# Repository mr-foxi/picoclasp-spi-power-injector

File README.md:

# picoclasp-spi-power-injector
This is a PCB designed as a picoclasp-molex 6pin SPI pass-through with external power injection from a JST-XHP4. Able to inject either 5VDC directly, or step down 8/36VDC. Contains a 2A fuse for circuitry protection, and a jumper header to select power input.

### Parts List
 - 8/36V-5V_2A = K7805-2000R3 (https://www.mornsun-power.com/html/pdf/K7805-2000R3.html)
 - Pico-Clasp Molex 6pin = 5013310607 (https://www.molex.com/content/dam/molex/molex-dot-com/products/automated/en-us/salesdrawingpdf/501/501331/5013310607_sd.pdf?inline)
 - Pico-Clasp Plug = 5013300600 (https://www.molex.com/content/dam/molex/molex-dot-com/products/automated/en-us/salesdrawingpdf/501/501330/5013300600_sd.pdf?inline)
 - JST-XH4 = S4B-XH-A-1 (https://www.digikey.com/en/products/detail/jst-sales-america-inc/S4B-XH-A-1/9961923)
 - JST Plug = XHP-4 (https://www.jst-mfg.com/product/pdf/eng/eXH.pdf)
 - FUSE_2A = ERB-RE2R00V (https://industrial.panasonic.com/cdbs/www-data/pdf/AFA0000/AFA0000C7.pdf)
 - 3pin Male PCB Jumper Header = XJ8B-0311 (https://www.mouser.com/datasheet/2/307/en_xg8-1539045.pdf)
 - 2pin Jumper = M7582-05 (https://www.mouser.com/datasheet/2/181/M7580-M7583-1134644.pdf)

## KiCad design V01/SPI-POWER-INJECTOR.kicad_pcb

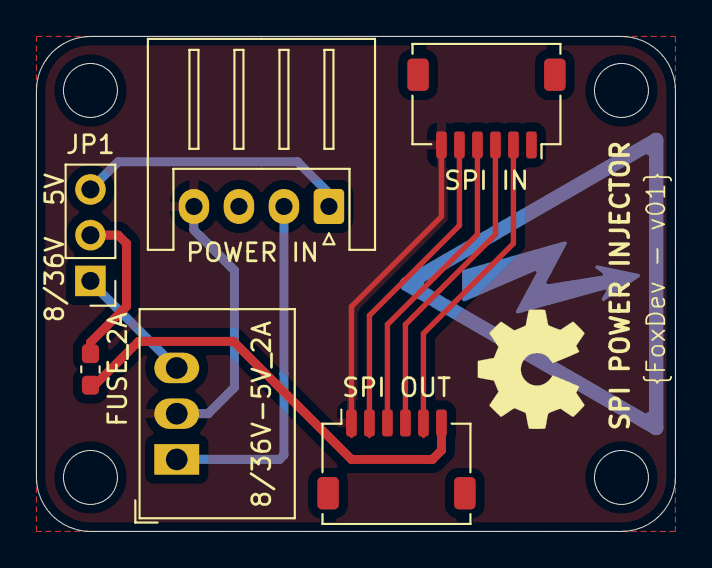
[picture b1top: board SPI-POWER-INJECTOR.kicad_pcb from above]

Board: 2 copper layers, 35.5 x 27.5 mm, 5 parts (0 on the bottom side), 5 nets.

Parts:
8/36V-5V_2A: K7805-2000R3; Converter_DCDC_RECOM_R-78B-2.0_THT
FUSE_2A: Fuse_0603_1608Metric_Pad1.05x0.95mm_HandSolder
JP1: PinHeader_1x03_P2.54mm_Vertical
POWER IN: JST_XH_S4B-XH-A_1x04_P2.50mm_Horizontal
SPI IN: Molex_Pico-Clasp_202396-0607_1x06-1MP_P1.00mm_Hor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; Molex_Pico-Clasp_202396-0607_1x06-1MP_P1.00mm_Horizontal

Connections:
5VIN: JP1.3, POWER IN.1
5VOLT: 8/36V-5V_2A.3, JP1.1
12VIN: 8/36V-5V_2A.1, POWER IN.2
FUSE: FUSE_2A.1, JP1.2
GND: 8/36V-5V_2A.2, POWER IN.4, SPI IN.6
